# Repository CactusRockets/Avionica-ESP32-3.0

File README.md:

# Placas da aviônica para o foguete Turing-500m

Nesse repositório temos os arquivos das placas que farão parte da aviônica do foguete Turing de 500m da Cactus Rockets Design.

### Descrição

Temos duas placas principais para esta aviônica:
- Placa de Processamento
- Placa de Acionamento

A placa de processamento é responsável pelo processamento dos dados dos módulos, armazenamento desses dados e telemetria. A placa de acionamento possui o circuito necessário para a correta ativação do Skib.

OBS.: Os arquivos das placas podems ser abertos por meio software Eagle da Autodesk.

### Esquemáticos e layouts

### Conexões entre placas

### Funcionamento

A placa de processamento contém um switch de ativação do sistema. No momento que o switch é pressionado, o sistema liga e faz a leitura dos módulos. Após cada leitura, ele armazena esses valores no microSD e envia esses dados via telemetria.

No momento que a placa de processamento detectar uma queda, ela envia um sinal para a placa de acionamento para que a mesma ative o Skib da parte de recuperação.

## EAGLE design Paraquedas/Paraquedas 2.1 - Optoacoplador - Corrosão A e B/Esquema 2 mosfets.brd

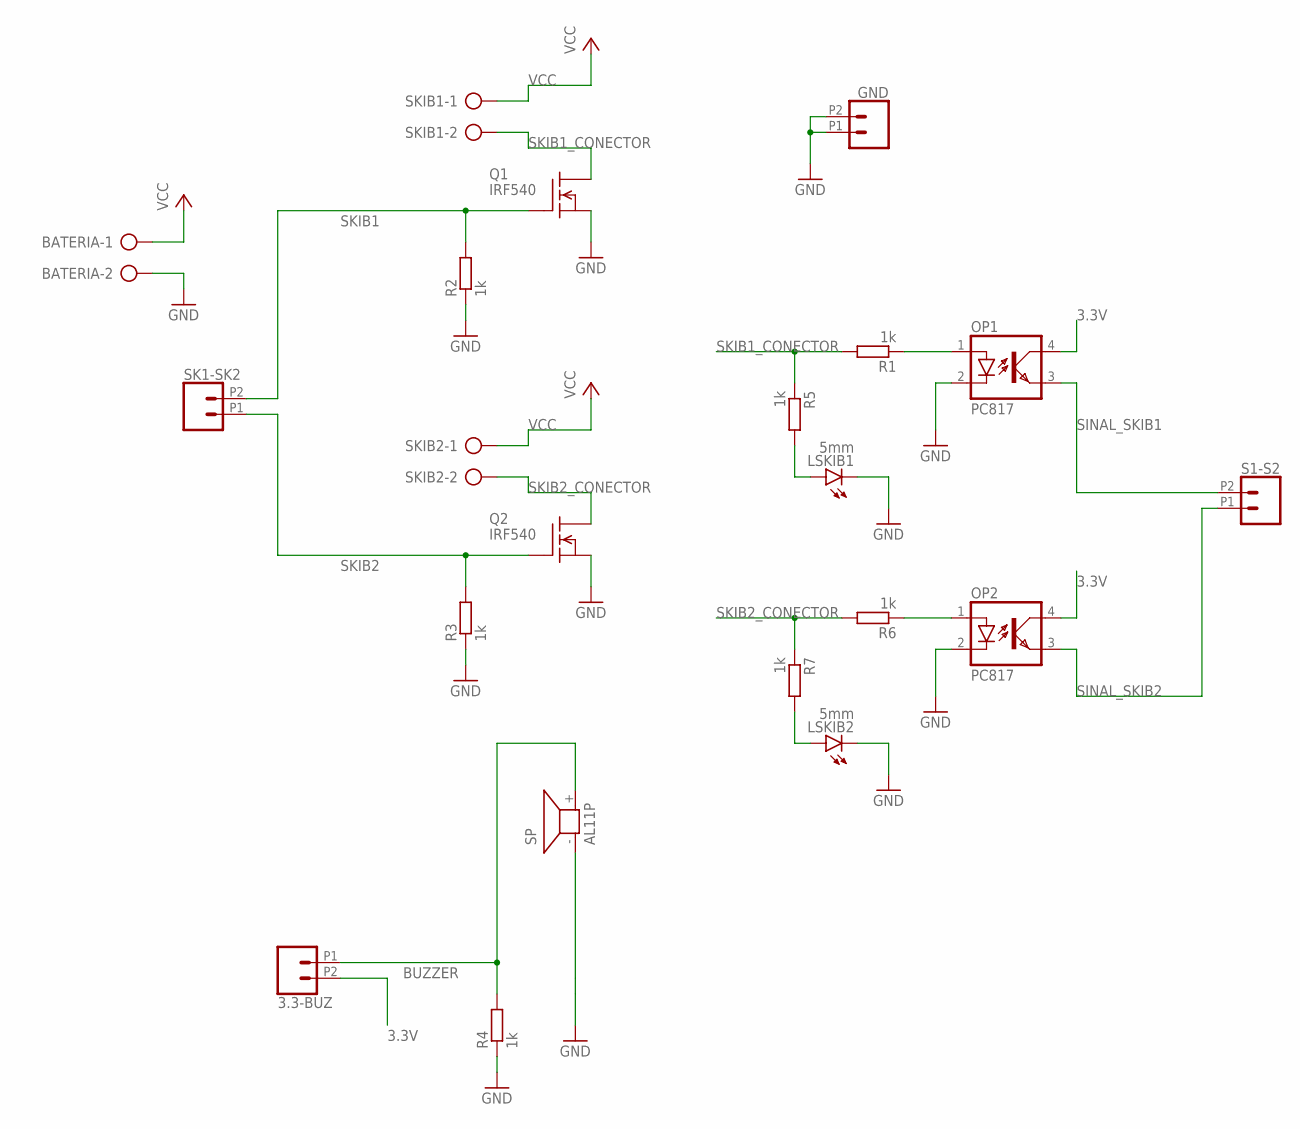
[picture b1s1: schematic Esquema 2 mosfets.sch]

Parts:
3.3-BUZ: CONN_022.54MM_SCREWTERM; 1X02_2.54_SCREWTERM
BATERIA: AK500/2-H
GND: CONN_022.54MM_SCREWTERM; 1X02_2.54_SCREWTERM
LSKIB1, LSKIB2: 5mm; LED5MM
OP1, OP2: PC817; DIL04
Q1, Q2: IRF540; TO220
R1, R2, R3, R4, R5, R6, R7: 1k; 0207/10
S1-S2: CONN_022.54MM_SCREWTERM; 1X02_2.54_SCREWTERM
SK1-SK2: CONN_022.54MM_SCREWTERM; 1X02_2.54_SCREWTERM
SKIB1, SKIB2: AK500/2-H
SP: AL11P

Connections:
3.3V: 3.3-BUZ.P2 (2), OP1.4 (COL), OP2.4 (COL)
BUZZER: 3.3-BUZ.P1 (1), R4.2, SP.+ (2)
GND: BATERIA.2, LSKIB1.K (C), LSKIB2.K (C), OP1.2 (C), OP2.2 (C), Q1.3 (S), Q2.3 (S), R2.1, R3.1, R4.1, SP.- (1)
unnamed: LSKIB2.A, R7.2
unnamed: GND.P1 (1), GND.P2 (2)
unnamed: LSKIB1.A, R5.2
unnamed: OP1.1 (A), R1.1
unnamed: OP2.1 (A), R6.1
SINAL_SKIB1: OP1.3 (EMIT), S1-S2.P2 (2)
SINAL_SKIB2: OP2.3 (EMIT), S1-S2.P1 (1)
SKIB1: Q1.1 (G), R2.2, SK1-SK2.P2 (2)
SKIB1_CONECTOR: Q1.2 (D), R1.2, R5.1, SKIB1.2
SKIB2: Q2.1 (G), R3.2, SK1-SK2.P1 (1)
SKIB2_CONECTOR: Q2.2 (D), R6.2, R7.1, SKIB2.2
VCC: BATERIA.1, SKIB1.1, SKIB2.1

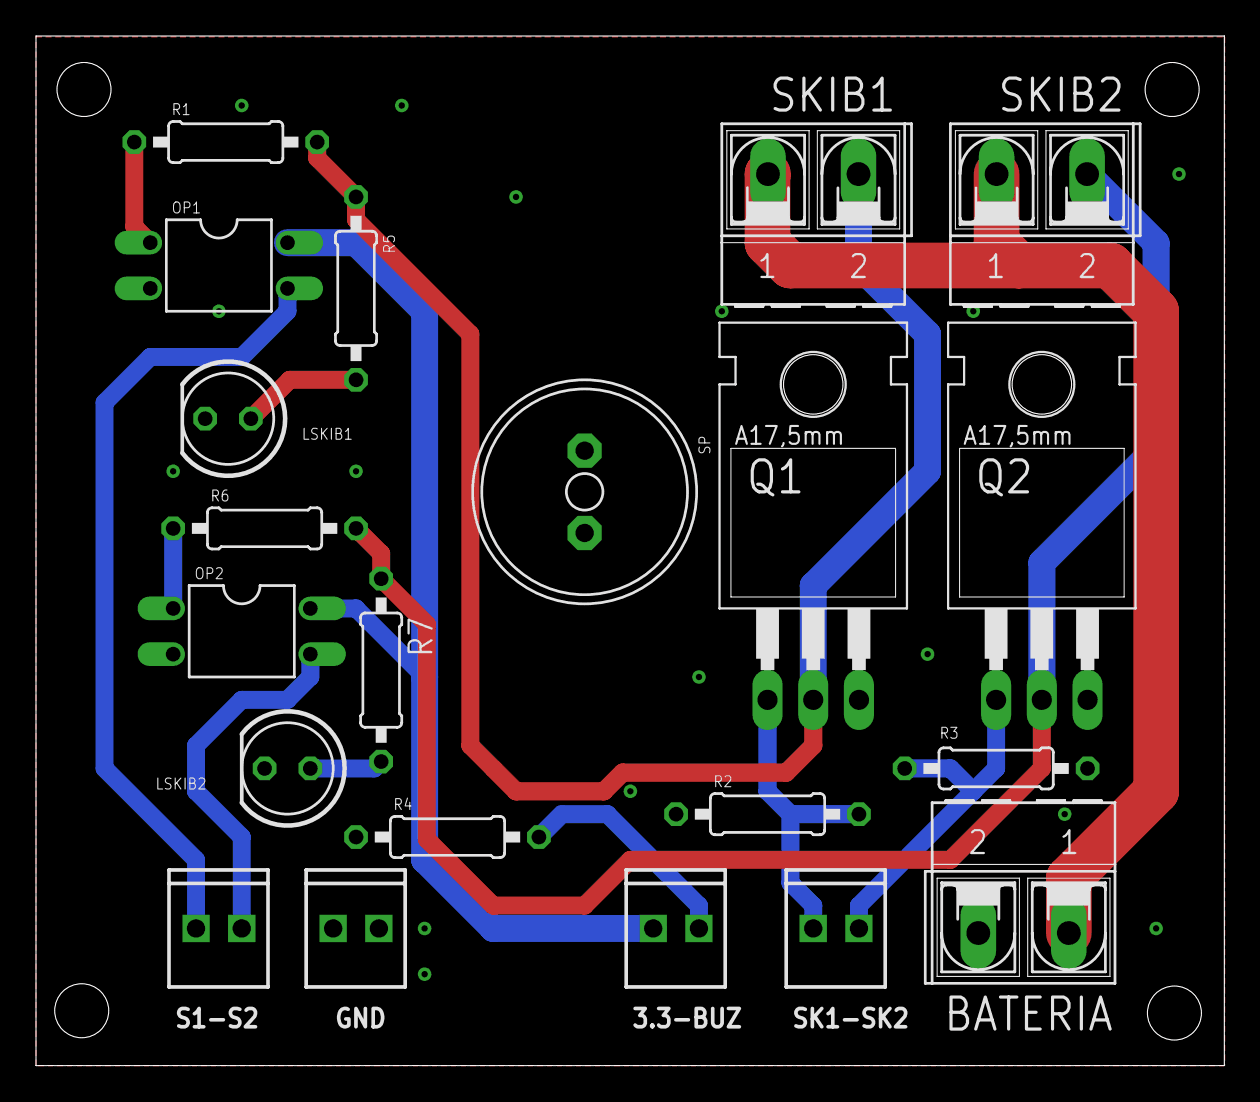
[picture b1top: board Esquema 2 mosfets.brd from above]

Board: 2 copper layers, 66.0 x 57.2 mm, 21 parts (0 on the bottom side), 15 nets.

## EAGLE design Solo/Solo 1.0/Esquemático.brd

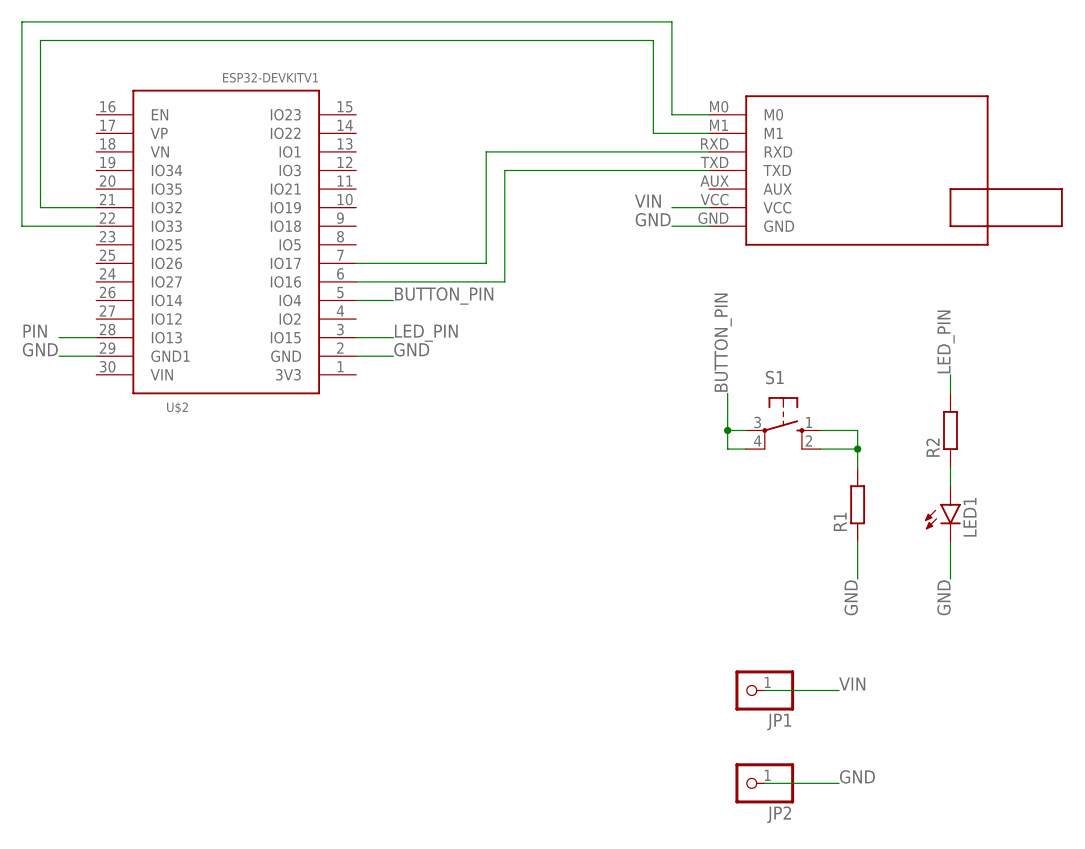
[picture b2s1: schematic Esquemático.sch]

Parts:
JP1, JP2: PINHD-1X1; 1X01
LED1: LED5MM
R1, R2: R-EU_0207/10; 0207/10
S1: 10-XX; B3F-10XX
U$1: E22-400T30D; E22-400T30D_FOOTPRINT
U$2: ESP32DEVKITV1; ESP32-DEVKITV1

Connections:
BUTTON_PIN: S1.3, S1.4 (P1), U$2.5 (IO4)
GND: JP2.1, LED1.K (C), R1.1, U$1.GND, U$2.2 (GND), U$2.29 (GND1)
LED_PIN: R2.2, U$2.3 (IO15)
unnamed: R1.2, S1.1 (S), S1.2 (S1)
unnamed: LED1.A, R2.1
unnamed: U$1.TXD, U$2.6 (IO16)
unnamed: U$1.RXD, U$2.7 (IO17)
unnamed: U$1.M0, U$2.22 (IO33)
unnamed: U$1.M1, U$2.21 (IO32)
PIN: U$2.28 (IO13)
VIN: JP1.1, U$1.VCC

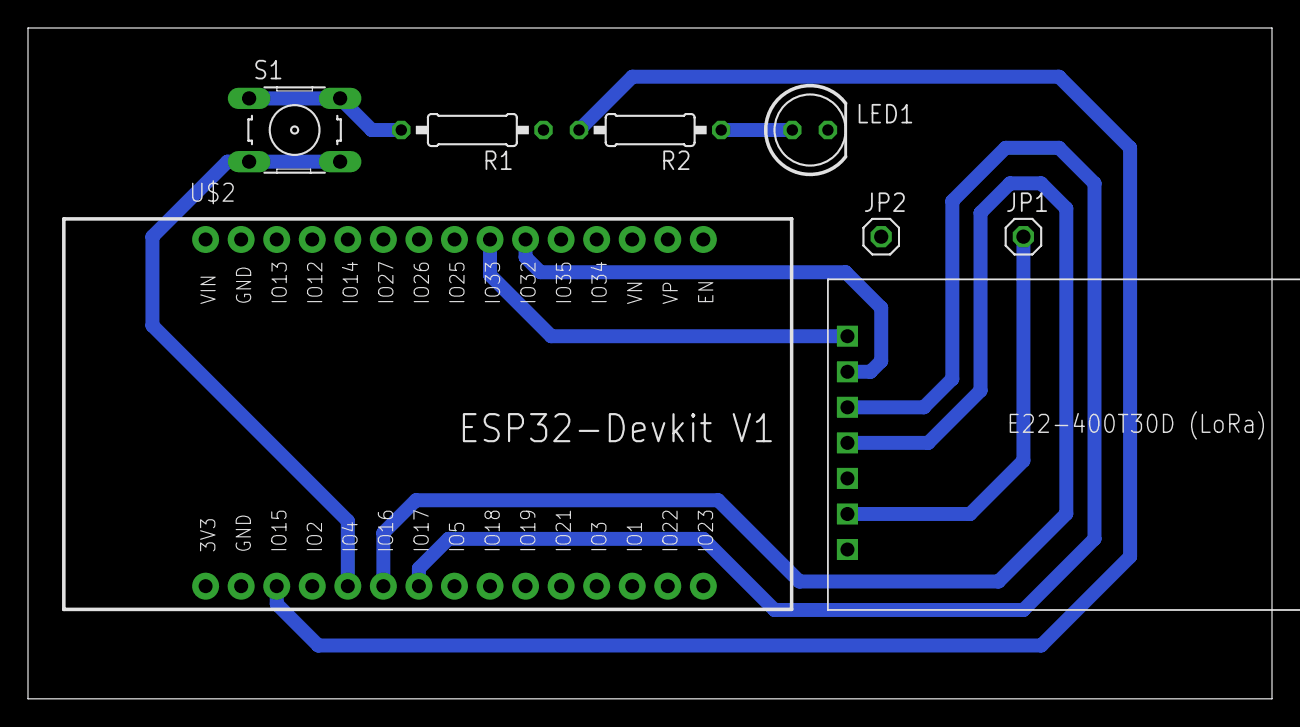
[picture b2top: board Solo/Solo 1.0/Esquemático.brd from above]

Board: 2 copper layers, 88.9 x 47.9 mm, 8 parts (0 on the bottom side), 10 nets.

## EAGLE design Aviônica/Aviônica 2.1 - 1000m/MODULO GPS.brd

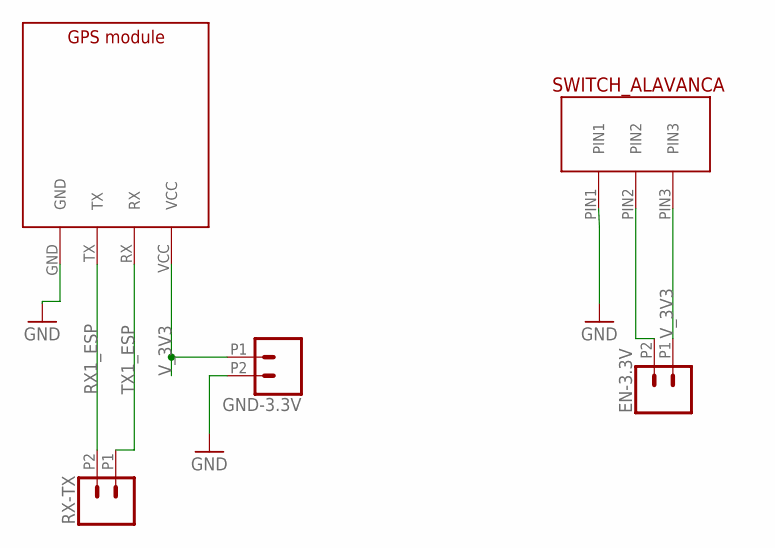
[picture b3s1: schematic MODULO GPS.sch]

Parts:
EN-3.3V: CONN_022.54MM_SCREWTERM; 1X02_2.54_SCREWTERM
GND-3.3V: CONN_022.54MM_SCREWTERM; 1X02_2.54_SCREWTERM
RX-TX: CONN_022.54MM_SCREWTERM; 1X02_2.54_SCREWTERM
U$1: SWITCH_ALAVANCA; SWITCH_ALAVANCA_FOOTPRINT
U$3: GPS_MODULE; GPS_MODULE_FOOTPRINT

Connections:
ENABLE_SIGNAL: EN-3.3V.P2 (2), U$1.PIN2
GND: GND-3.3V.P2 (2), U$1.PIN1, U$3.GND
RX1_ESP: RX-TX.P2 (2), U$3.TX
TX1_ESP: RX-TX.P1 (1), U$3.RX
V_3V3: EN-3.3V.P1 (1), GND-3.3V.P1 (1), U$1.PIN3, U$3.VCC

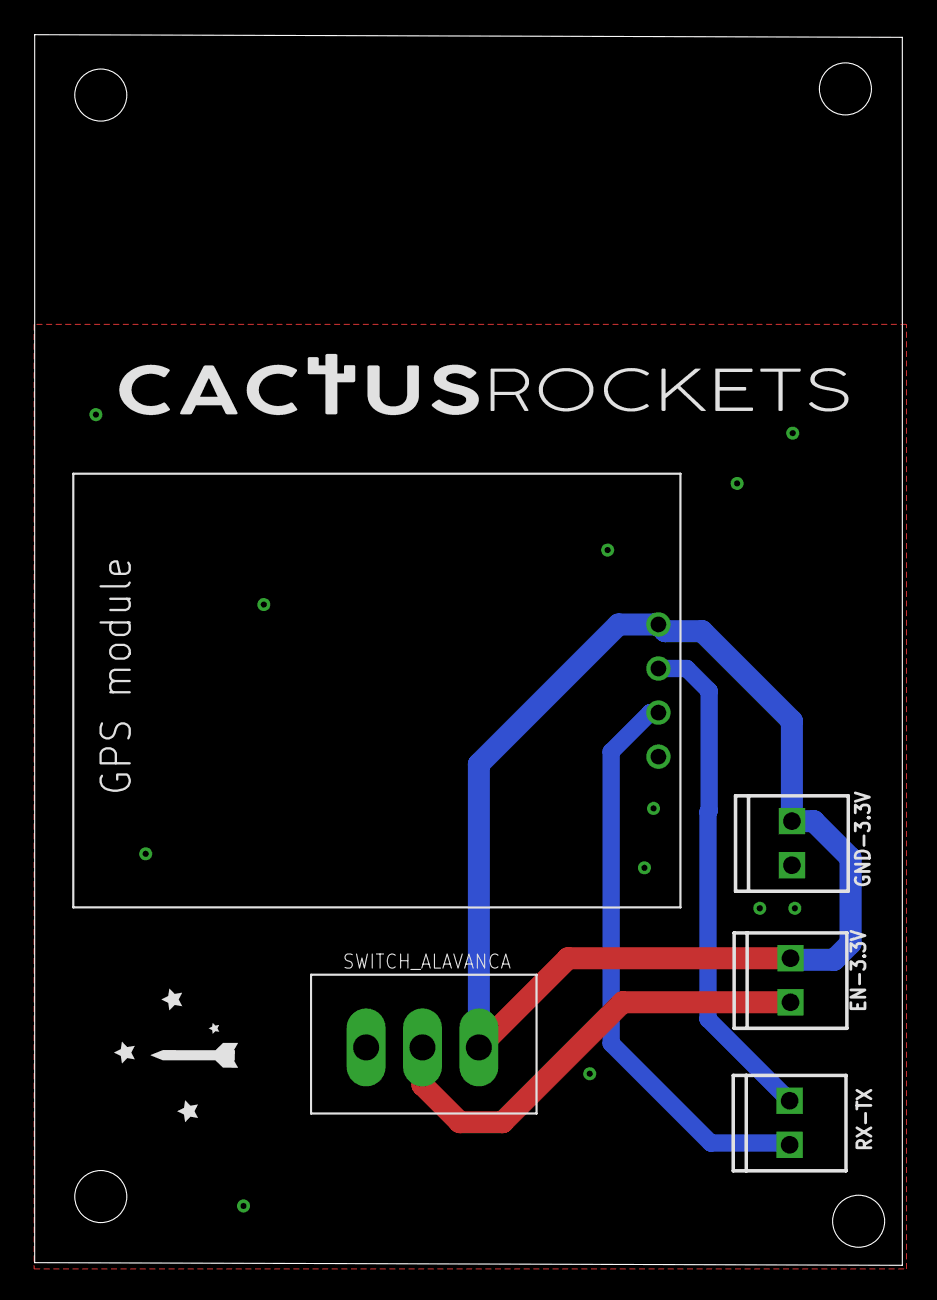
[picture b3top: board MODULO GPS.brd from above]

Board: 2 copper layers, 50.0 x 70.9 mm, 5 parts (0 on the bottom side), 5 nets.

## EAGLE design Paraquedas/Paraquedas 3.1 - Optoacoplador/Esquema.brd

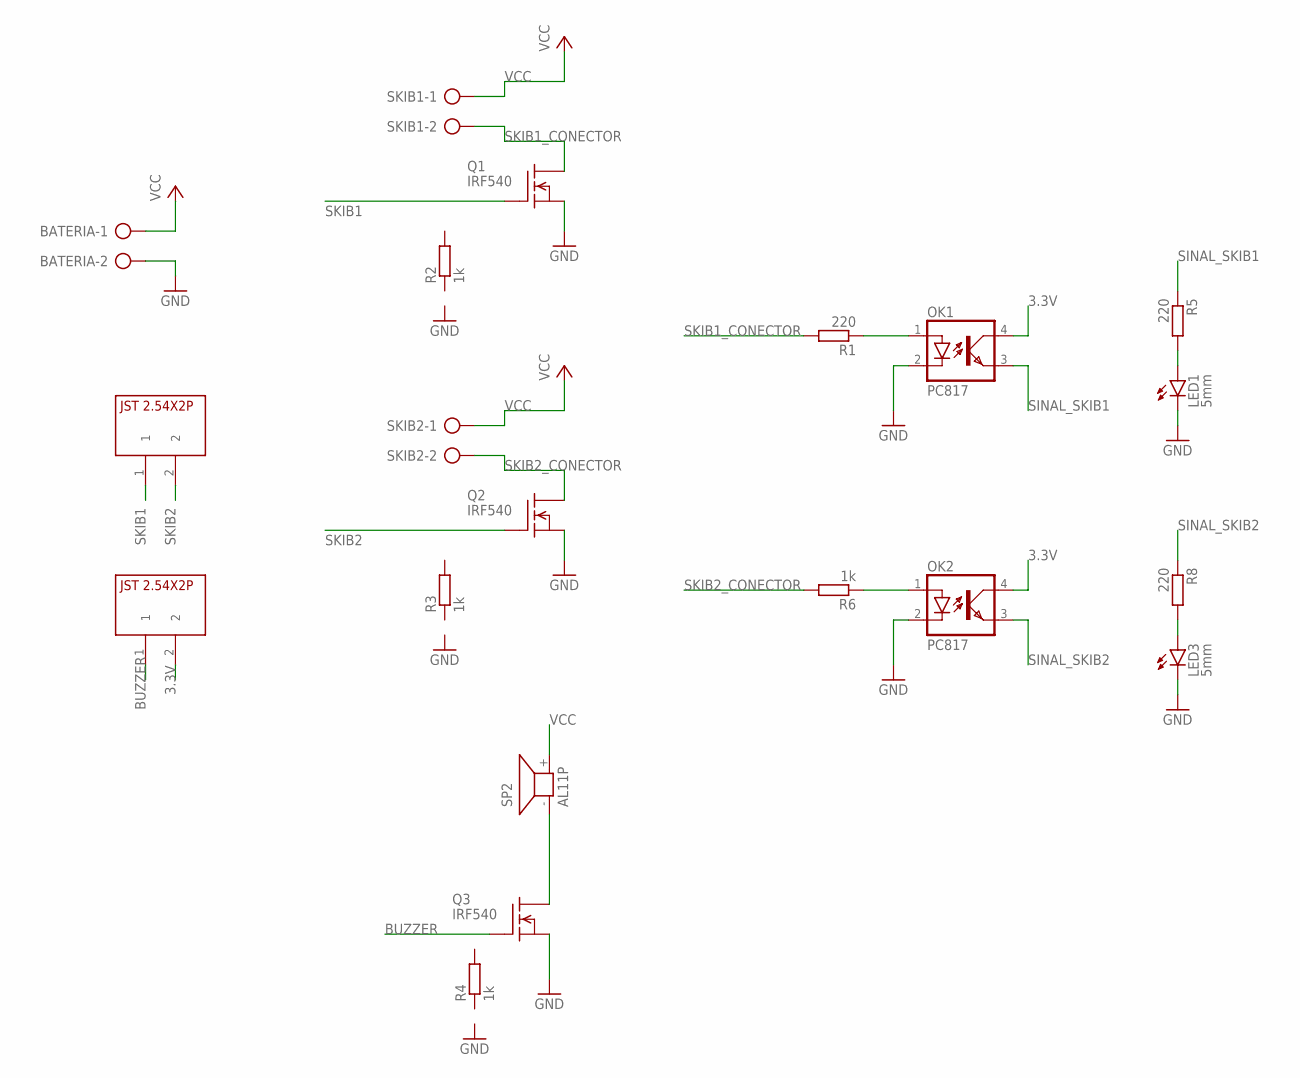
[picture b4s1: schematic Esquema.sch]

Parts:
BATERIA: AK500/2-H
LED1, LED3: 5mm; LED5MM
OK1, OK2: PC817; DIL04
Q1, Q2, Q3: IRF540; TO220
R1, R5, R8: 220; 0207/10
R2, R3, R4, R6: 1k; 0207/10
SKIB1, SKIB2: AK500/2-H
SP2: AL11P
U$1, U$2: JST2.54X2P; JST2.54X2P_FOOTPRINT

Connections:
3.3V: OK1.4 (COL), OK2.4 (COL), U$1.2
BUZZER: Q3.1 (G), U$1.1
GND: BATERIA.2, LED1.K (C), LED3.K (C), OK1.2 (C), OK2.2 (C), Q1.3 (S), Q2.3 (S), Q3.3 (S)
unnamed: Q3.2 (D), SP2.- (1)
unnamed: LED3.A, R8.2
unnamed: OK1.1 (A), R1.1
unnamed: OK2.1 (A), R6.1
unnamed: LED1.A, R5.2
SINAL_SKIB1: OK1.3 (EMIT), R5.1
SINAL_SKIB2: OK2.3 (EMIT), R8.1
SKIB1: Q1.1 (G), U$2.1
SKIB1_CONECTOR: Q1.2 (D), R1.2, SKIB1.2
SKIB2: Q2.1 (G), U$2.2
SKIB2_CONECTOR: Q2.2 (D), R6.2, SKIB2.2
VCC: BATERIA.1, SKIB1.1, SKIB2.1, SP2.+ (2)

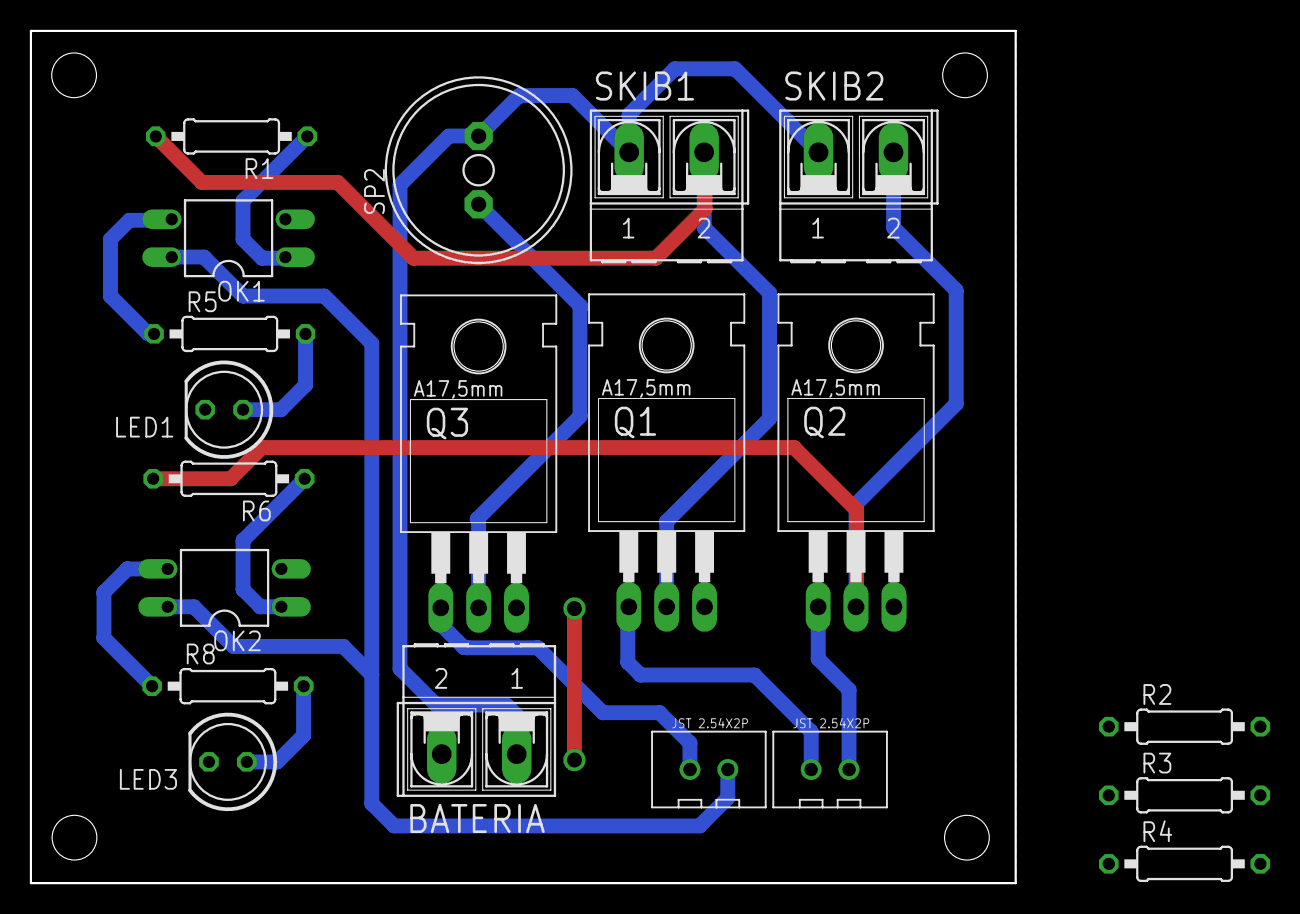
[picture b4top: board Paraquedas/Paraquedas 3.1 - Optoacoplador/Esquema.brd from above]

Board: 2 copper layers, 66.0 x 57.1 mm, 20 parts (0 on the bottom side), 15 nets.

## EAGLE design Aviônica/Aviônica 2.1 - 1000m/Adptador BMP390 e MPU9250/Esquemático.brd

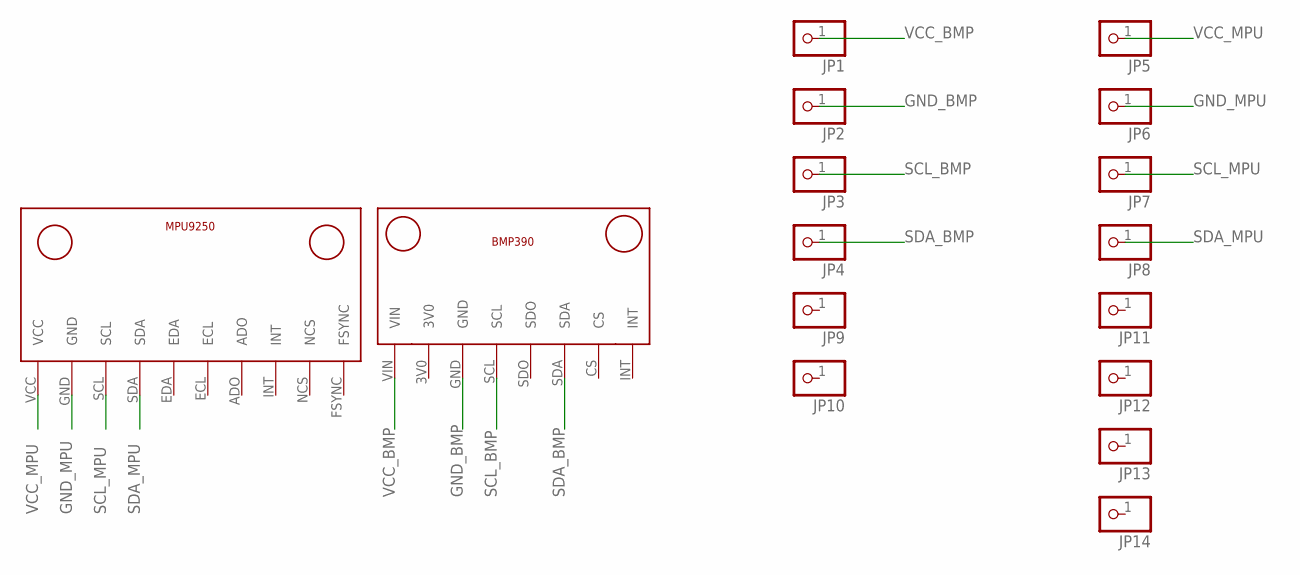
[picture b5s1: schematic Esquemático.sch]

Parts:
JP1, JP2, JP3, JP4, JP5, JP6, JP7, JP8, JP9, JP10, JP11, JP12, JP13, JP14: PINHD-1X1; 1X01
U$3: BMP390V1; BMP390_FOOTPRINT
U$4: MPU9250V1; MPU9250_FOOTPRINT

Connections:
GND_BMP: JP2.1, U$3.GND
GND_MPU: JP6.1, U$4.GND
SCL_BMP: JP3.1, U$3.SCL
SCL_MPU: JP7.1, U$4.SCL
SDA_BMP: JP4.1, U$3.SDA
SDA_MPU: JP8.1, U$4.SDA
VCC_BMP: JP1.1, U$3.VIN
VCC_MPU: JP5.1, U$4.VCC

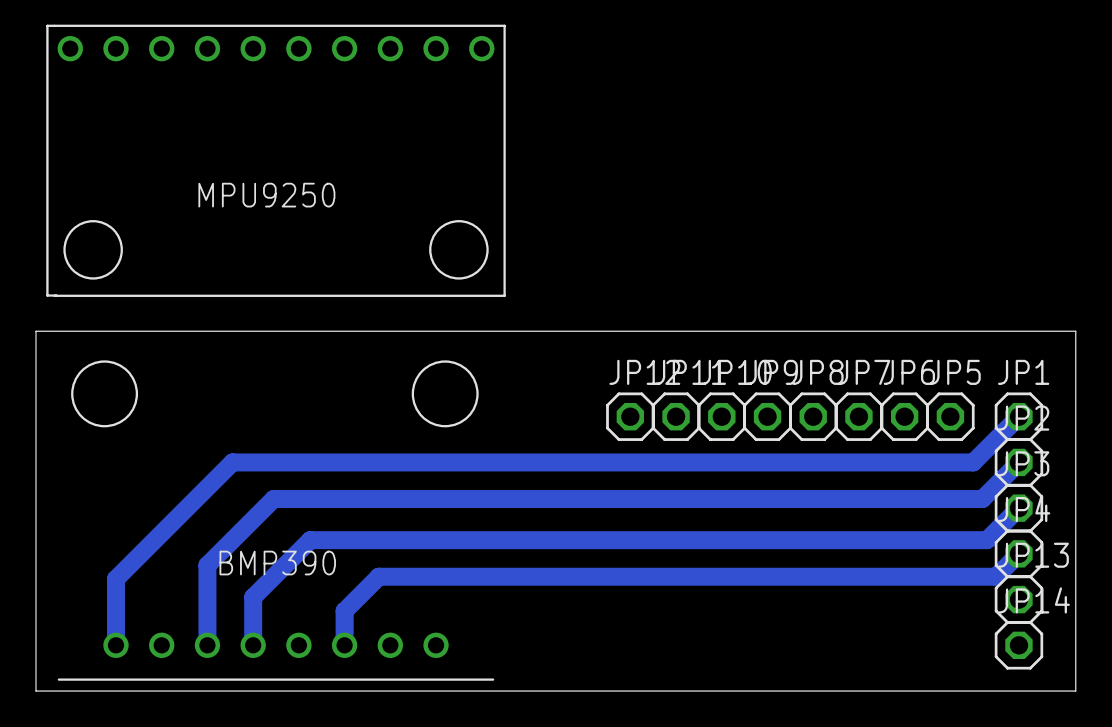
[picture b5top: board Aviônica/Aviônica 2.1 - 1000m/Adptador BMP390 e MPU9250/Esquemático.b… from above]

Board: 2 copper layers, 57.8 x 20.0 mm, 16 parts (0 on the bottom side), 8 nets.

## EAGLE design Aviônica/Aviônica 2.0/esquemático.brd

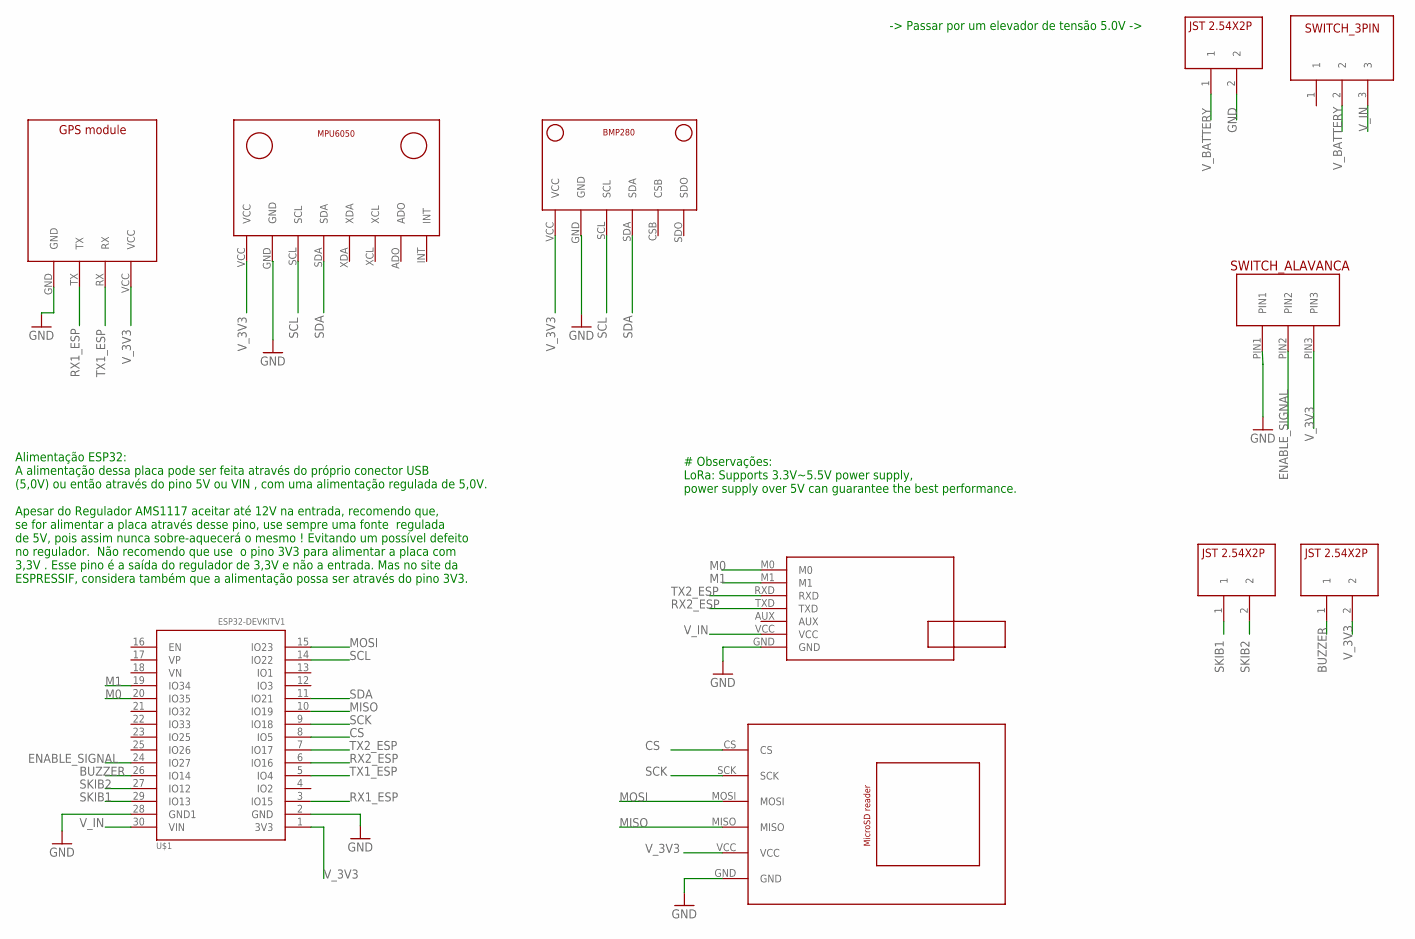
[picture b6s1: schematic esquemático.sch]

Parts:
U$1: ESP32DEVKITV1; ESP32-DEVKITV1
U$2: E22-400T30D; E22-400T30D_FOOTPRINT
U$3: GPS_MODULE; GPS_MODULE_FOOTPRINT
U$4: BMP280V1; BMP280_FOOTPRINT
U$5: SWITCH_ALAVANCA; SWITCH_ALAVANCA_FOOTPRINT
U$6: MPU6050V1; MPU6050_FOOTPRINT
U$7: MICROSD_READER; MICROSD_READER_FOOTPRINT
U$8, U$9, U$12: JST2.54X2P; JST2.54X2P_FOOTPRINT
U$11: SWITCH_3PIN

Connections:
BUZZER: U$1.26 (IO14), U$9.1
CS: U$1.8 (IO5), U$7.CS
ENABLE_SIGNAL: U$1.24 (IO27), U$5.PIN2
GND: U$1.2 (GND), U$1.28 (GND1), U$2.GND, U$3.GND, U$4.GND, U$5.PIN1, U$6.GND, U$7.GND, U$12.2
M0: U$1.20 (IO35), U$2.M0
M1: U$1.19 (IO34), U$2.M1
MISO: U$1.10 (IO19), U$7.MISO
MOSI: U$1.15 (IO23), U$7.MOSI
RX1_ESP: U$1.3 (IO15), U$3.TX
RX2_ESP: U$1.6 (IO16), U$2.TXD
SCK: U$1.9 (IO18), U$7.SCK
SCL: U$1.14 (IO22), U$4.SCL, U$6.SCL
SDA: U$1.11 (IO21), U$4.SDA, U$6.SDA
SKIB1: U$1.29 (IO13), U$8.1
SKIB2: U$1.27 (IO12), U$8.2
TX1_ESP: U$1.5 (IO4), U$3.RX
TX2_ESP: U$1.7 (IO17), U$2.RXD
V_3V3: U$1.1 (3V3), U$3.VCC, U$4.VCC, U$5.PIN3, U$6.VCC, U$7.VCC, U$9.2
V_BATTERY: U$11.2, U$12.1
V_IN: U$1.30 (VIN), U$2.VCC, U$11.3

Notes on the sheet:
-> Passar por um elevador de tensão 5.0V ->
# Observações: LoRa: Supports 3.3V~5.5V power supply, power supply over 5V can guarantee the best performance.
Alimentação ESP32: A alimentação dessa placa pode ser feita através do próprio conector USB (5,0V) ou então através do pino 5V ou VIN , com uma alimentação regulada de 5,0V. Apesar do Regulador AMS1117 aceitar até 12V na entrada, recomendo que, se for alimentar a placa através desse pino, use sempr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

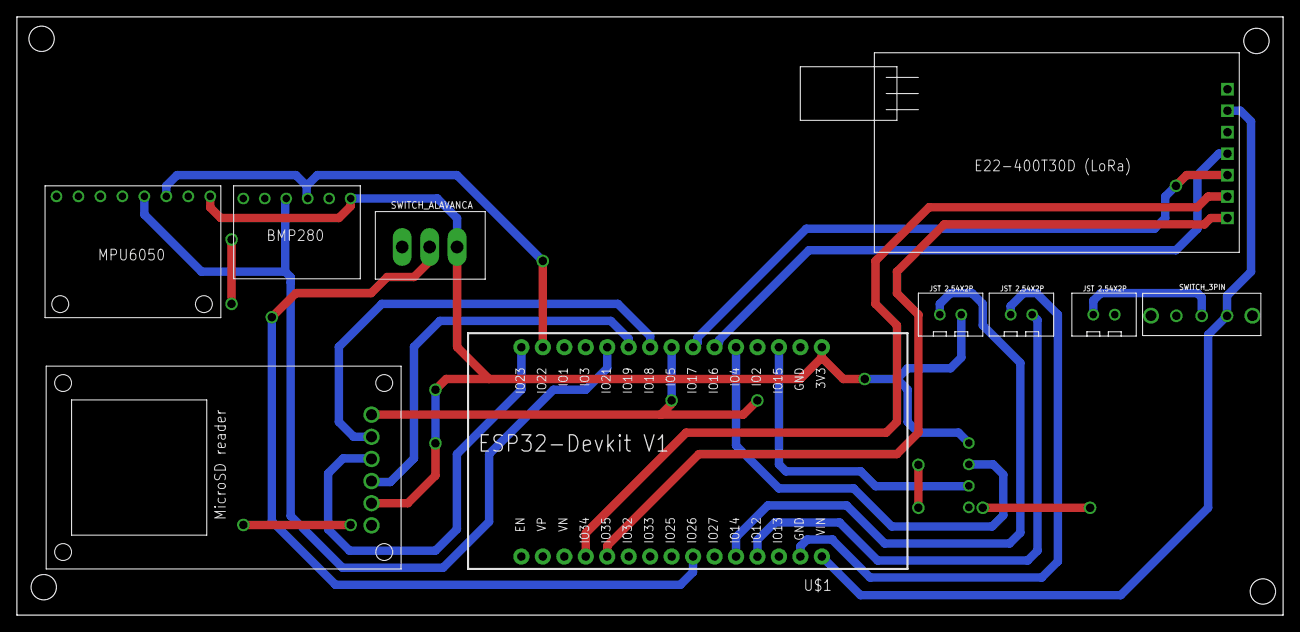
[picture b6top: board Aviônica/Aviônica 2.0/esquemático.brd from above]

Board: 2 copper layers, 149.8 x 70.8 mm, 11 parts (1 on the bottom side), 20 nets.

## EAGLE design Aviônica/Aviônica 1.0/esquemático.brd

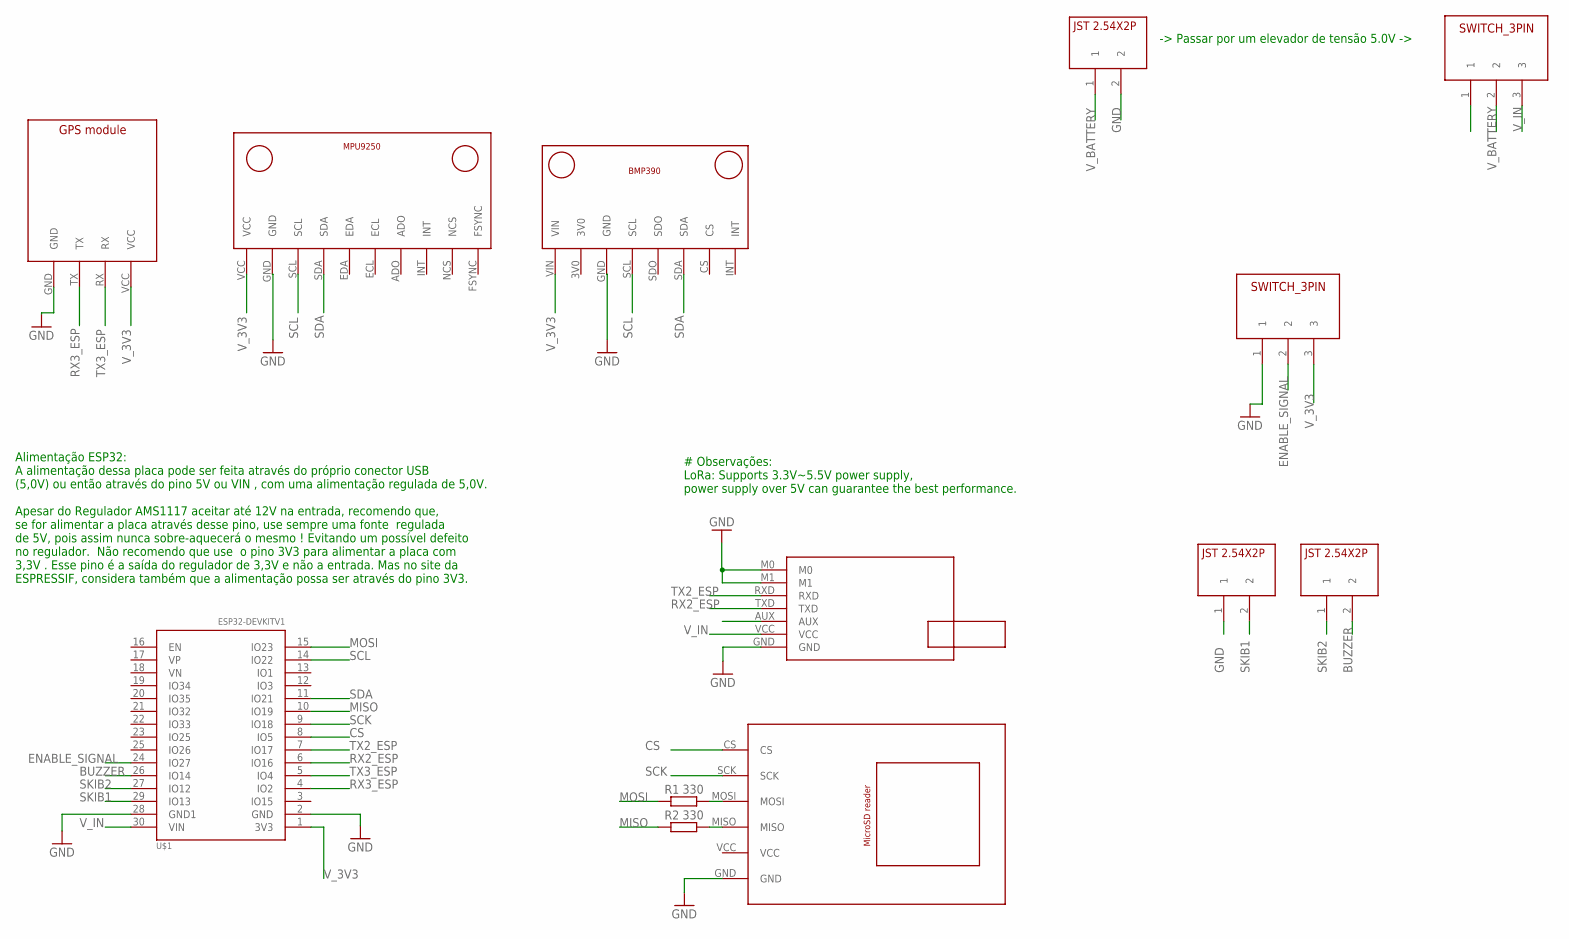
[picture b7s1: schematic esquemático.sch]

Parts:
R1, R2: 330; 0207/10
U$1: ESP32DEVKITV1; ESP32-DEVKITV1
U$2: E22-400T30D; E22-400T30D_FOOTPRINT
U$3: GPS_MODULE; GPS_MODULE_FOOTPRINT
U$5: BMP390V1; BMP390_FOOTPRINT
U$6: MPU9250V1; MPU9250_FOOTPRINT
U$7: MICROSD_READER; MICROSD_READER_FOOTPRINT
U$8, U$9, U$12: JST2.54X2P; JST2.54X2P_FOOTPRINT
U$10, U$11: SWITCH_3PIN

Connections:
BUZZER: U$1.26 (IO14), U$9.2
CS: U$1.8 (IO5), U$7.CS
ENABLE_SIGNAL: U$1.24 (IO27), U$10.2
GND: U$1.2 (GND), U$1.28 (GND1), U$2.GND, U$2.M0, U$2.M1, U$3.GND, U$5.GND, U$6.GND, U$7.GND, U$8.1, U$10.1, U$12.2
MISO: R2.1, U$1.10 (IO19)
MOSI: R1.1, U$1.15 (IO23)
unnamed: R1.2, U$7.MOSI
unnamed: R2.2, U$7.MISO
RX2_ESP: U$1.6 (IO16), U$2.TXD
RX3_ESP: U$1.4 (IO2), U$3.TX
SCK: U$1.9 (IO18), U$7.SCK
SCL: U$1.14 (IO22), U$5.SCL, U$6.SCL
SDA: U$1.11 (IO21), U$5.SDA, U$6.SDA
SKIB1: U$1.29 (IO13), U$8.2
SKIB2: U$1.27 (IO12), U$9.1
TX2_ESP: U$1.7 (IO17), U$2.RXD
TX3_ESP: U$1.5 (IO4), U$3.RX
V_3V3: U$1.1 (3V3), U$3.VCC, U$5.VIN, U$6.VCC, U$10.3
V_BATTERY: U$11.2, U$12.1
V_IN: U$1.30 (VIN), U$2.VCC, U$11.3

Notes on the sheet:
-> Passar por um elevador de tensão 5.0V ->
# Observações: LoRa: Supports 3.3V~5.5V power supply, power supply over 5V can guarantee the best performance.
Alimentação ESP32: A alimentação dessa placa pode ser feita através do próprio conector USB (5,0V) ou então através do pino 5V ou VIN , com uma alimentação regulada de 5,0V. Apesar do Regulador AMS1117 aceitar até 12V na entrada, recomendo que, se for alimentar a placa através desse pino, use sempr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

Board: 2 copper layers, 13 parts (0 on the bottom side), 20 nets, no tracks yet.

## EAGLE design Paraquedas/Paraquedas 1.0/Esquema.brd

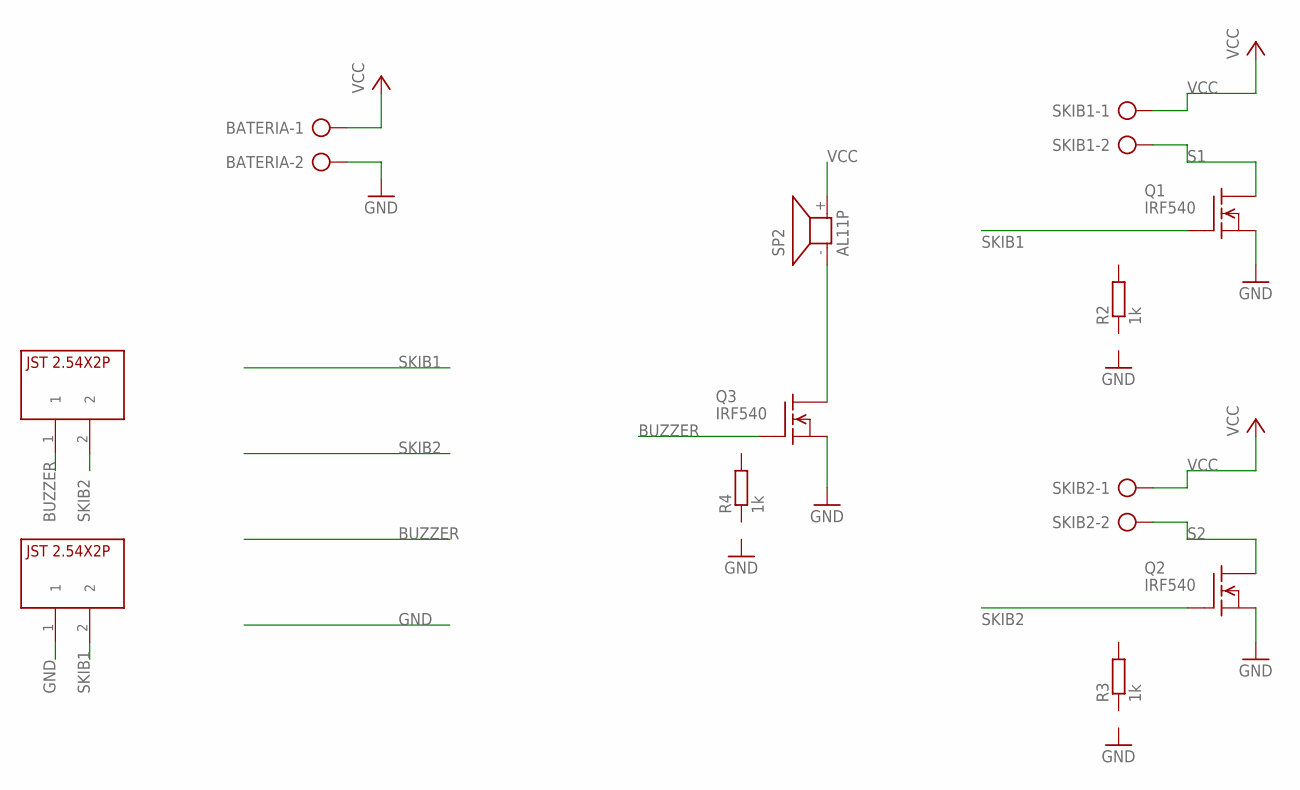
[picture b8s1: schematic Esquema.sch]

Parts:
BATERIA: AK500/2-H
Q1, Q2, Q3: IRF540; TO220
R2, R3, R4: 1k; 0207/10
SKIB1, SKIB2: AK500/2-H
SP2: AL11P
U$1, U$2: JST2.54X2P; JST2.54X2P_FOOTPRINT

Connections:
BUZZER: Q3.1 (G), U$1.1
GND: BATERIA.2, Q1.3 (S), Q2.3 (S), Q3.3 (S), U$2.1
unnamed: Q3.2 (D), SP2.- (1)
S1: Q1.2 (D), SKIB1.2
S2: Q2.2 (D), SKIB2.2
SKIB1: Q1.1 (G), U$2.2
SKIB2: Q2.1 (G), U$1.2
VCC: BATERIA.1, SKIB1.1, SKIB2.1, SP2.+ (2)

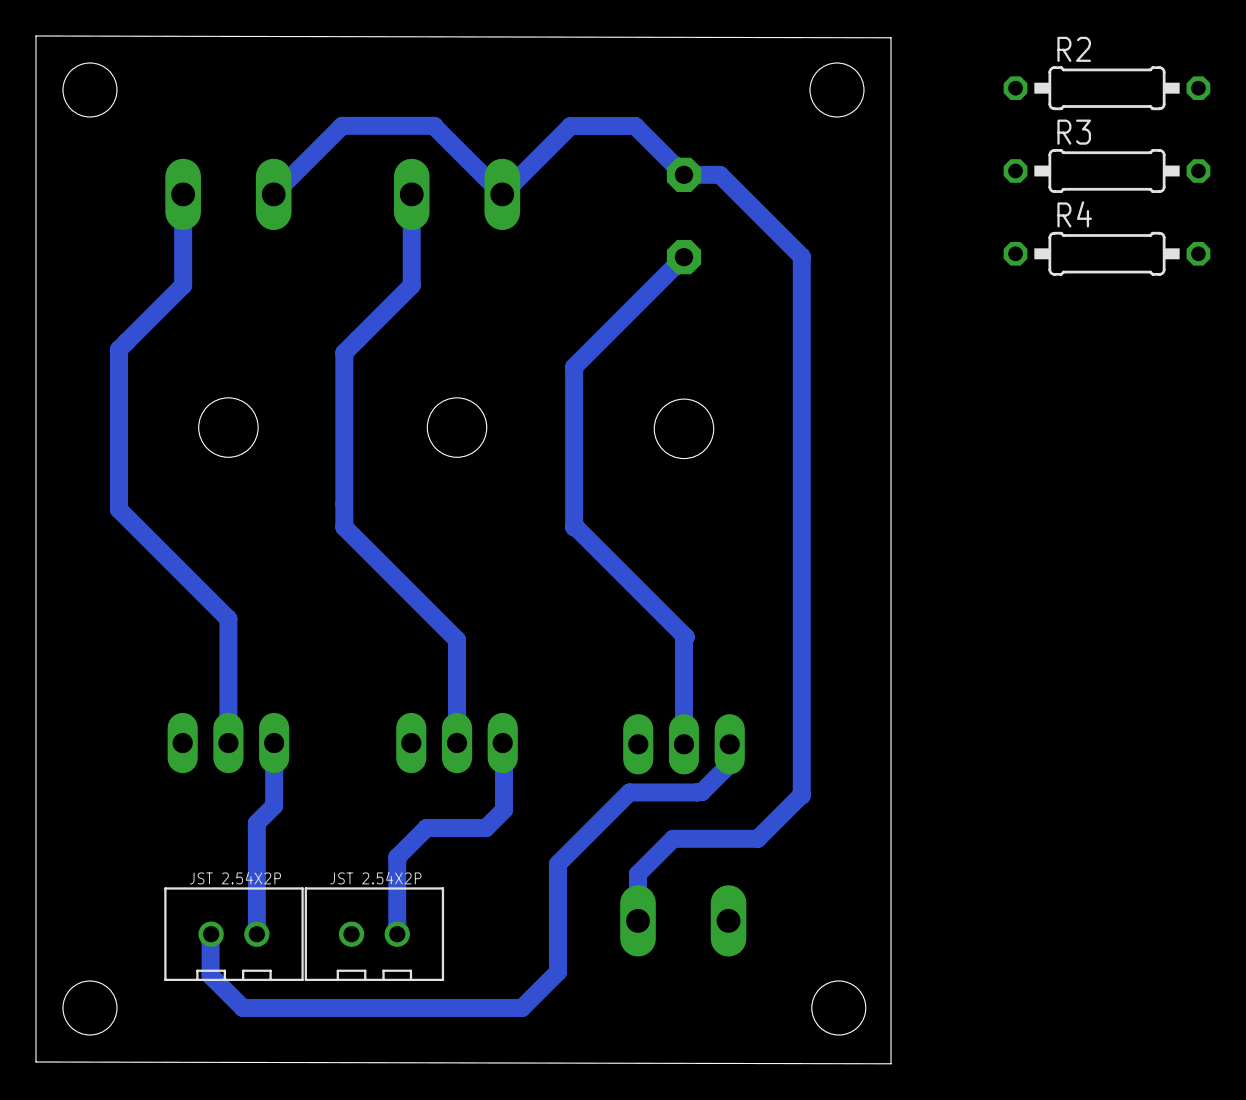
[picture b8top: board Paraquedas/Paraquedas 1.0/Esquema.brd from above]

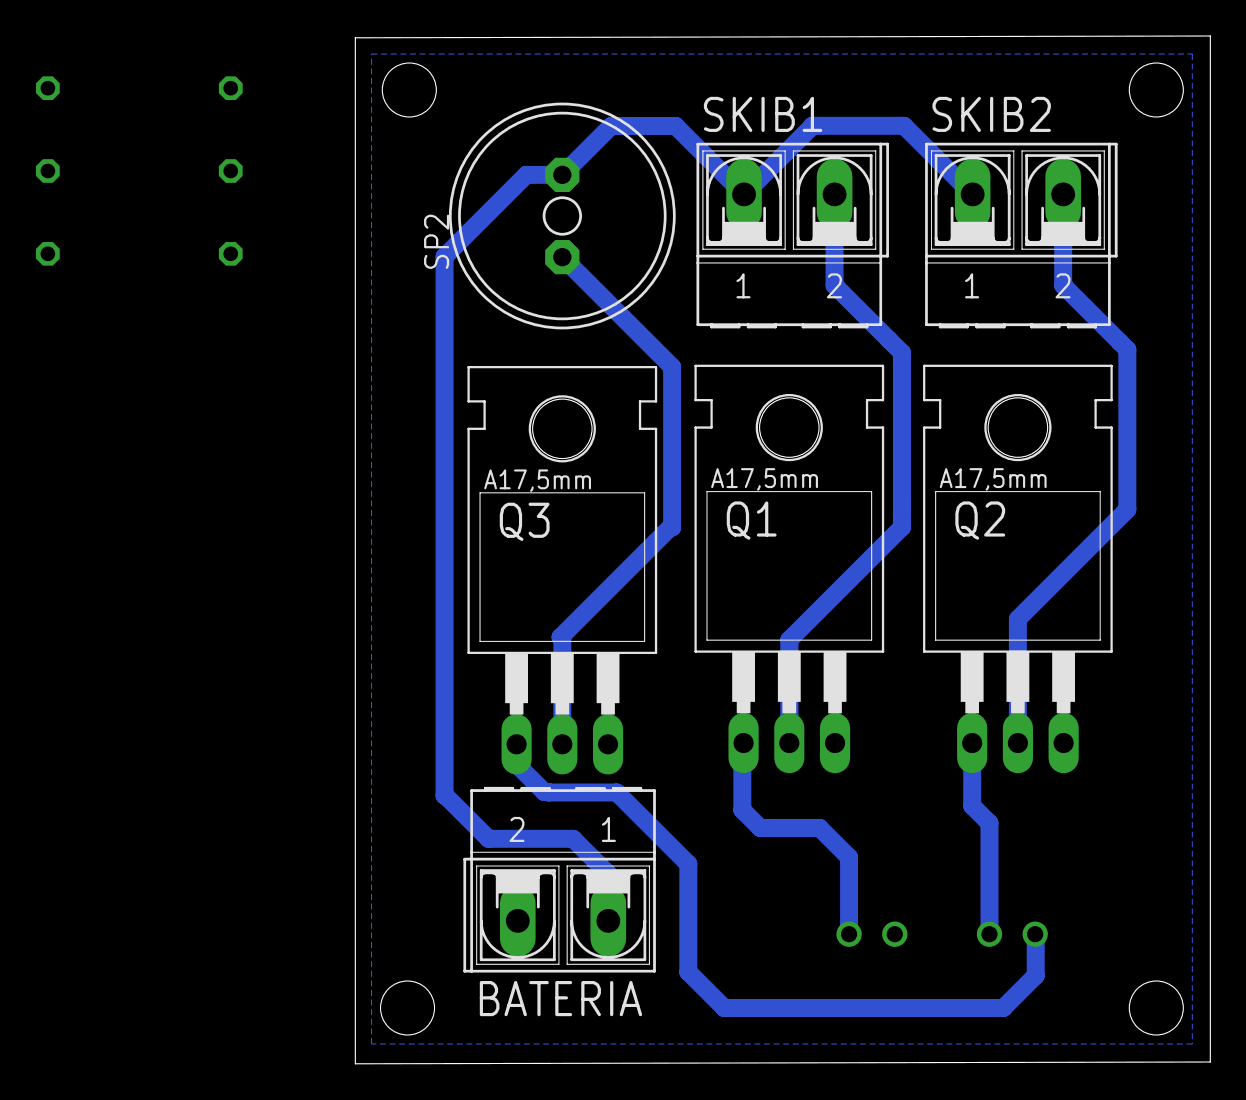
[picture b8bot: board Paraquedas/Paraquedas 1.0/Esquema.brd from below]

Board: 2 copper layers, 47.5 x 57.1 mm, 12 parts (7 on the bottom side), 8 nets.

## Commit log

2023-07-28 Push
2023-07-30 Message
2023-07-31 avionicav2.2
2023-07-31 Update paraquedas
2023-08-01 Atualização-avionica
2023-08-01 atualização Avionica
2023-08-01 correções avionica e paraquedas
2023-08-10 Atualização de trilhas
2023-11-14 Upgrade
2024-04-16 Create Esquema 2 mosfets

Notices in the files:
parts and their libraries:
SparkFun-Connectors: Licensing: Creative Commons ShareAlike 4.0 International - https://creativecommons.org/licenses/by-sa/4.0
